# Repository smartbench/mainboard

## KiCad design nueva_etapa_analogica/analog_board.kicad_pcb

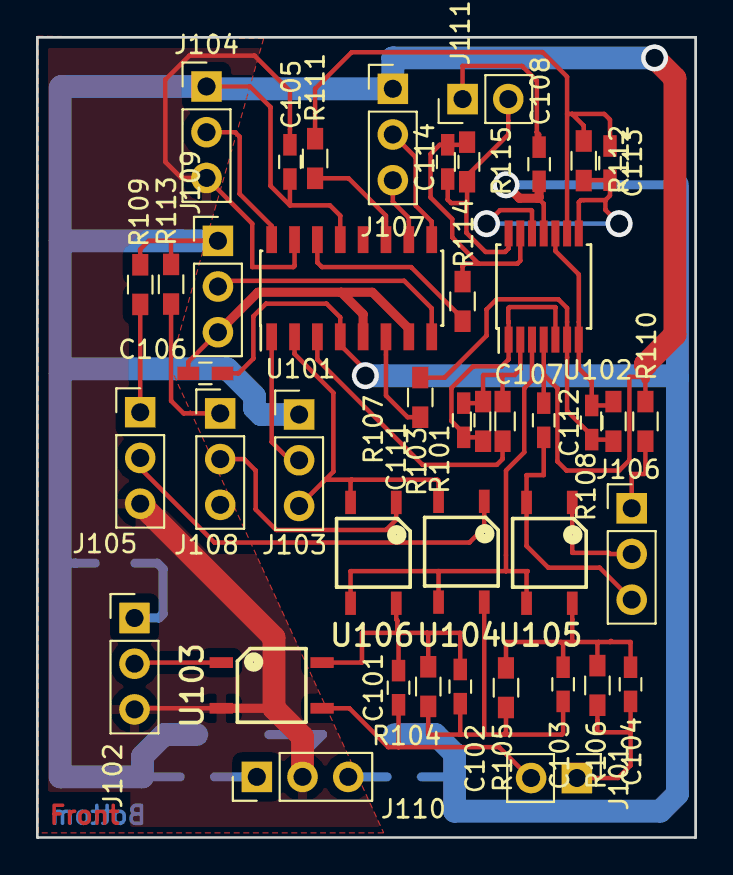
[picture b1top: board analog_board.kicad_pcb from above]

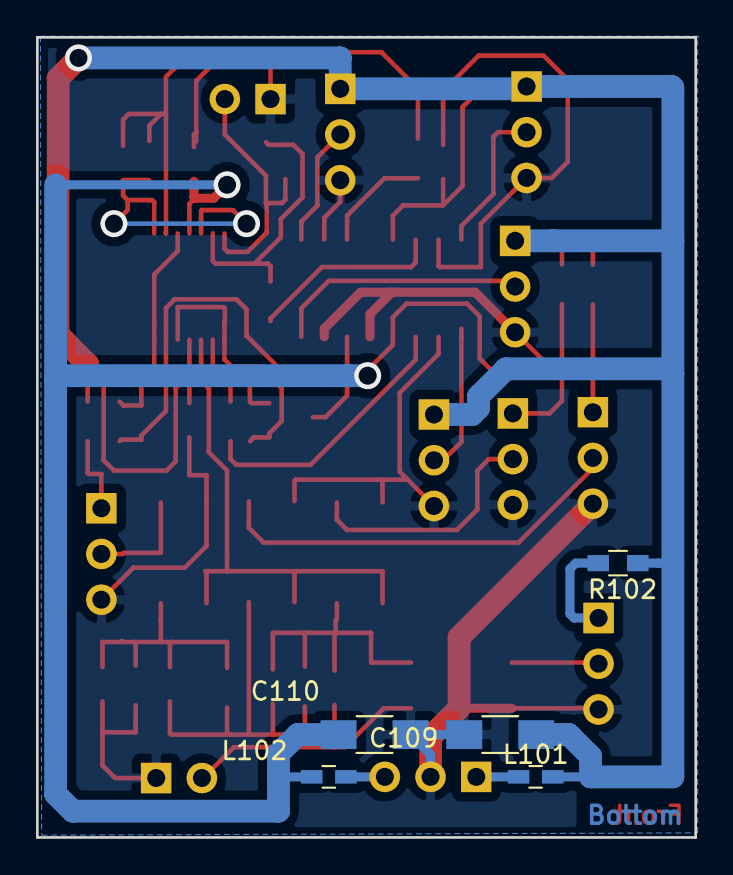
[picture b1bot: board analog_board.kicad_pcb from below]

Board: 2 copper layers, 36.6 x 44.5 mm, 48 parts (5 on the bottom side), 34 nets.

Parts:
C101, C105, C106, C107, C108: 100nF; C_0603_HandSoldering
C102: 22pF; C_0603_HandSoldering
C103: 180pF; C_0603_HandSoldering
C104: 1800pF; C_0603_HandSoldering
C109, C110: 10uF 10V Tantalum; C_1206_HandSoldering
C111, C112, C113, C114: 10pF; C_0603_HandSoldering
J101, J111: Conn_01x02; Pin_Header_Straight_1x02_Pitch2.54mm
J102, J103, J104, J105, J106, J107, J108, J109, J110: Conn_01x03; Pin_Header_Straight_1x03_Pitch2.54mm
L101, L102: BLM18AG121SN1D; C_0603_HandSoldering
R101, R107, R111, R114: 2K2; R_0603_HandSoldering
R102, R109, R110, R113: 1K; R_0603_HandSoldering
R103, R108, R112: 4K7; R_0603_HandSoldering
R104: 887K; R_0603_HandSoldering
R105: 90K9; R_0603_HandSoldering
R106, R115: 10K; R_0603_HandSoldering
U101: MAX4522CSE+; SOIC-16_3.9x9.9mm_Pitch1.27mm
U102: TLV3544; TSSOP-14_4.4x5mm_Pitch0.65mm
U103, U104, U105, U106: CPC1017N; 2.54SOP4

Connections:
/Vatt: U102.3, U104.3, U105.3, U106.3
/Vin_coupled: C101.1, C102.1, R104.2, U103.4, U106.4
GND: C104.2, C105.2, C106.1, C107.2, C108.1, C109.2, C110.1, J101.1, J102.3, J103.3, J104.3, J105.3, J106.3, J107.3, J108.3, J109.3, J110.2, J111.1, R106.1, U101.2, U101.5, U101.7, U101.10, U101.15, U103.2, U104.2, U105.2, U106.2
unnamed: C101.2, J101.2, U103.3
unnamed: C102.2, C103.1, R104.1, R105.2, U104.4
unnamed: C103.2, C104.1, R105.1, R106.2, U105.4
unnamed: C111.1, R101.2, R103.2, U102.2
unnamed: C111.2, R103.1, U102.1, U102.5
unnamed: C112.1, R107.2, R108.2, U102.6
unnamed: C112.2, R108.1, U102.7, U102.10
unnamed: C113.1, R111.2, R112.2, U102.9
unnamed: C113.2, R112.1, U102.8, U102.12
unnamed: C114.1, R114.2, R115.2, U102.13
unnamed: C114.2, J111.2, R115.1, U102.14
unnamed: J102.1, R102.1
unnamed: J102.2, U103.1
unnamed: J103.2, U101.1
unnamed: J104.2, U101.16
unnamed: J105.1, R109.1
unnamed: J105.2, U104.1
unnamed: J106.1, R110.1
unnamed: J106.2, U105.1
unnamed: J107.2, U101.9
unnamed: J108.1, R113.1
unnamed: J108.2, U106.1
unnamed: J109.2, U101.8
unnamed: J110.1, L101.1
unnamed: J110.3, L102.1
unnamed: R101.1, U101.3
unnamed: R107.1, U101.6
unnamed: R111.1, U101.11
unnamed: R114.1, U101.14
VDD: C105.1, C107.1, C109.1, J103.1, J104.1, J107.1, J109.1, L101.2, R102.2, R109.2, R110.2, R113.2, U101.13, U102.4
VSS: C106.2, C108.2, C110.2, L102.2, U101.4, U102.11

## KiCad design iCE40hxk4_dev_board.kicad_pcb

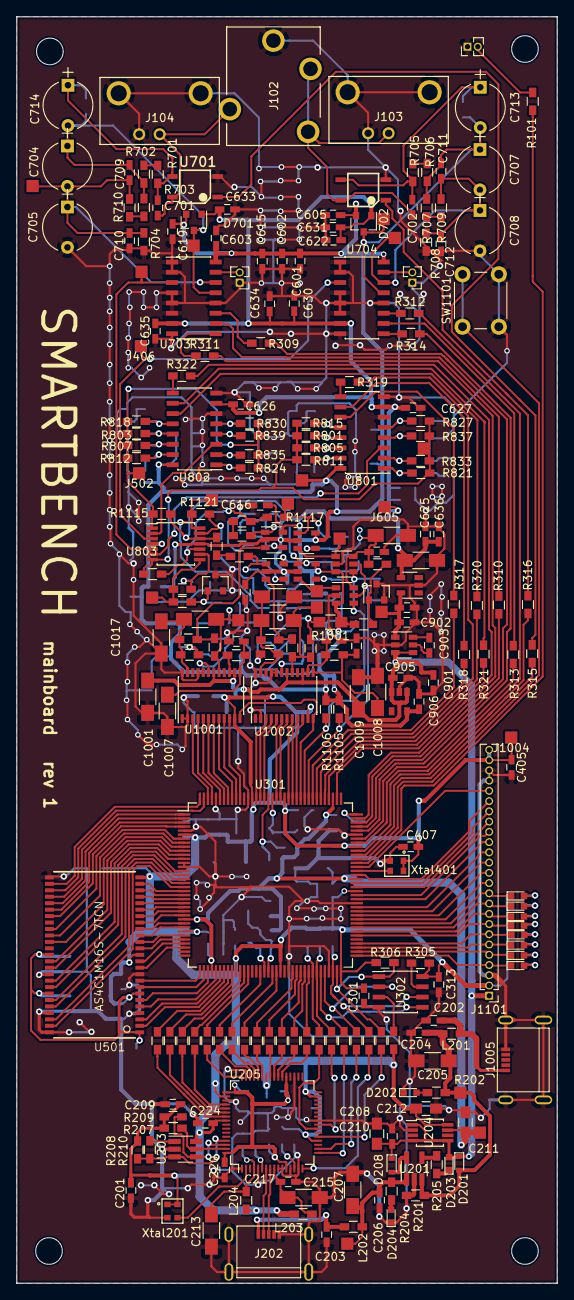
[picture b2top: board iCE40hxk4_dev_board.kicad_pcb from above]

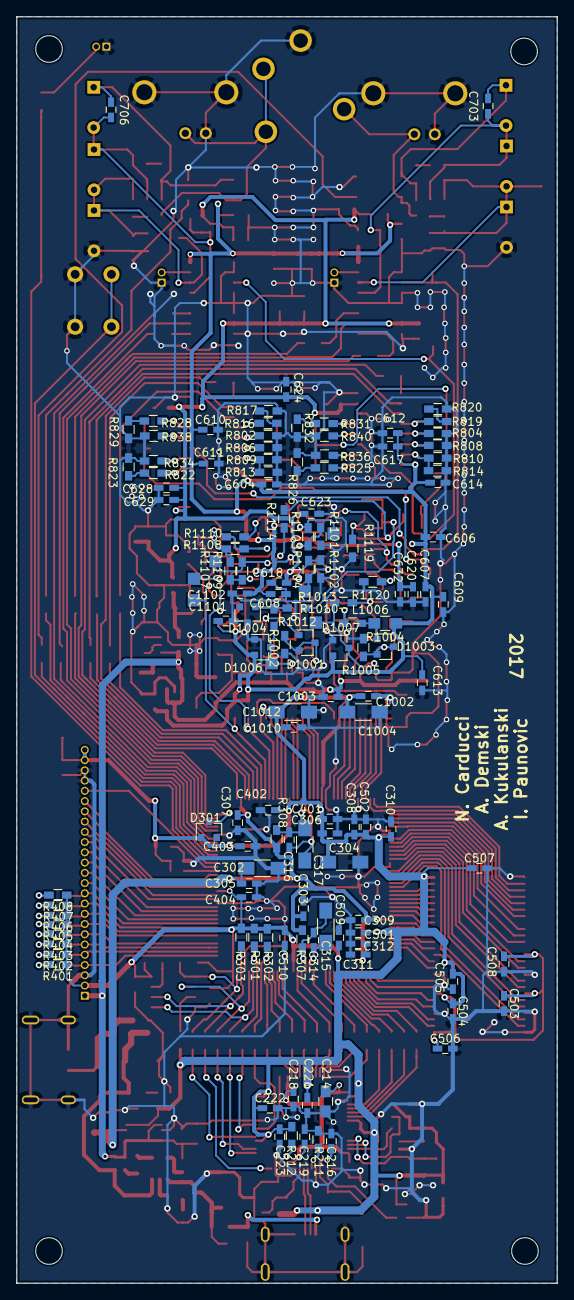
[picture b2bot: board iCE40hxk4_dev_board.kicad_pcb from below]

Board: 4 copper layers, 67.0 x 157.0 mm, 383 parts (133 on the bottom side), 266 nets.

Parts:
C201, C204, C206, C208, C209, C216, C217, C218, C219, C220, C221, C222, C223, C224, C301, C305, C307, C308, C309, C311, C313, C314, C316, C401, C402, C403, C404, C405, C407, C501, C502, C503, C504, C505, C506, C507, C508, C509, C510, C601, C603, C605, C606, C608, C612, C614, C616, C618, C619, C621, C623, C625, C627, C629, C631, C633, C635, C905, C1002, C1003, C1005, C1006, C1010, C1011, C1018, C1101, C1102: 100nF; C_0603_HandSoldering
C202, C203, C310, C312: 10nF; C_0603_HandSoldering
C205, C207, C213, C215: 4.7uF; C_1206_HandSoldering
C210, C211, C212: 2.2uF; C_0805_HandSoldering
C214: 4.7uF; C_0805_HandSoldering
C302, C304, C315, C317, C907, C1001, C1004, C1007, C1008, C1009, C1012, C1013, C1014, C1015, C1016, C1017: 10uF; C_1206_HandSoldering
C303, C306, C602, C604, C607, C609, C611, C613, C615, C617, C622, C624, C626, C628, C630, C632, C634, C636, C903, C904, C906: 1uF; C_0603_HandSoldering
C610, C620, C901, C902: 10uF; C_0603_HandSoldering
C701, C702: 100pF; C_0603_HandSoldering
C703, C706: 22pF; C_0603_HandSoldering
C704, C707: 1-3pF; CP_Radial_Tantal_D6.0mm_P5.00mm
C705, C708: 5-20pF; CP_Radial_Tantal_D6.0mm_P5.00mm
C709, C711: 180pF; C_0603_HandSoldering
C710, C712: 1800pF; C_0603_HandSoldering
C713, C714: Not used; CP_Radial_Tantal_D6.0mm_P5.00mm
D201, D208: D_Schottky_CDBURT0530LL-HF; D_0603
D202, D204, D401, D402, D403, D404, D405, D406, D407, D408: GREEN; LED_0603
D203: RED; LED_0603
D301: D_BAS21,215; D_SOT-23_ANK
D701, D702, D1006, D1007: D_Schottky_BAT54S-7-F; SOT-23
D1001, D1003: LM4040DYM3-2.5-TR; SOT-23
D1002: LM4041EIM3-1.2/NOPB; SOT-23
D1004, D1005: D_Schottky_BAT54-7-F; D_SOT-23_ANK
J101, J601, J602: CONN_01X02; Pin_Header_Straight_1x02_Pitch1.27mm
J102: Jack Estereo; KobiConn_161-3509-E_Jack_3.5mm
J103, J104: CONN_COAXIAL; BNC_1-1337543-0
J105, J106, J107, J108: MountingHole
J202: USB_OTG; USB_Micro-B_47642-0001
J401, J402, J403, J404, J405, J406, J501, J502, J603, J604, J605, J701, J702, J705, J706, J801, J802, J803, J804, J805, J806, J807, J808, J809, J810, J1001, J1002, J1003, J1004: Testpoint; TestPoint
J1005: USB_EXT; USB_Micro-B_47642-0001
J1101: CONN_01X25; Pin_Header_Straight_1x25_Pitch1.27mm
L201, L202, L203, L204: L_BLM18BA750SZ1D; L_0603_HandSoldering
L1001, L1002, L1003, L1004, L1005, L1006, L1007: L_BLM18AG121SN1D; L_0603_HandSoldering
R101, R201, R207, R209, R210, R301, R302, R303, R304, R305, R306, R704, R708, R1105, R1106, R1107, R1108, R1109, R1110: 10K; R_0603_HandSoldering
R202, R204, R205: 1K5; R_0603_HandSoldering
R208, R829, R832: 2K2; R_0603_HandSoldering
R211: 12K; R_0603_HandSoldering
R212, R309, R310, R311, R312, R313, R314, R315, R316, R317, R318, R319, R320, R321, R322, R827, R830, R1115, R1118: 1K; R_0603_HandSoldering
R213, R214, R215, R216, R217, R218, R219, R220, R221, R222, R223, R224, R225, R226, R227, R228, R229, R230, R231, R709, R710, R801, R803, R1002, R1005, R1103, R1104: 0R; R_0603_HandSoldering
R307, R308, R821, R823, R824, R826: 100R; R_0603_HandSoldering
R401, R402, R403, R404, R405, R406, R407, R408: 680R; R_0603_HandSoldering
R701, R705: 13K; R_0603_HandSoldering
R702, R706: 887K; R_0603_HandSoldering
R703, R707: 90K9; R_0603_HandSoldering
R802, R804, R1101, R1102: Let it open; R_0603_HandSoldering
R805, R806, R807, R808, R1010, R1011: 470R; R_0603_HandSoldering
R809, R810, R813, R814, R816, R819, R822, R825: 1K8; R_0603_HandSoldering
R811, R812, R815, R817, R818, R820, R1003, R1012, R1013: 220R; R_0603_HandSoldering
R828, R831: 47K; R_0603_HandSoldering
R833, R834, R835, R836, R837, R838, R839, R840: Not used; R_0603_HandSoldering
R1001, R1004: 50R; R_0805_HandSoldering
R1006, R1007, R1008, R1009, R1113, R1116: 4K7; R_0603_HandSoldering
R1111, R1112: 330R; R_0603_HandSoldering
R1114, R1117: 1K2; R_0603_HandSoldering
R1119, R1120: 6K8; R_0603_HandSoldering
R1121, R1122: 62K; R_0603_HandSoldering
SW1101: SW_Push; SW_PUSH_6mm_h4.3mm
U201: MIC2005A-2YM5; SOT-23-5_HandSoldering
U203: 93LC56BT-I/OT; SOT-23-6_Handsoldering
U204: MIC5355-S4YMME; MSOP-8_3x3mm_Pitch0.65mm
U205: FT2232H; LQFP-64_10x10mm_Pitch0.5mm
U301: iCE40-HX4K-TQ144; LQFP-144_20x20mm_Pitch0.5mm
U302: FLASH 2Mb; SOIC-8_3.9x4.9mm_Pitch1.27mm
U501: AS4C1M16S-7TCN; TSOP50-II
U701, U702: CPC1017N; 2.54SOP4
U703, U704, U801, U802: CD4051BM96; SOIC-16_3.9x9.9mm_Pitch1.27mm
U803: TLV3544IPWR; TSSOP-14_4.4x5mm_Pitch0.65mm
U901: LM2776DBVR; SOT-23-6
U902: MIC5317-2.5YM5-TR; SC-74(5-pins)
U903: TPS72325DBVR; SOT-23-5
U1001, U1002: ADC1175; TSSOP-24_4.4x7.8mm_Pitch0.65mm
U1101, U1102, U1105, U1106: MIC7300; SOT-23-5
U1103, U1104: MCP4716; SOT-23-6
Xtal201, Xtal401: LFSPXO019966; VLGA_4_2.5x2.0mm

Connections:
+1.8V: C214.1, C218.1, C219.1, C220.1, U205.12, U205.37, U205.49, U205.64
+3V3: C201.1, C209.1, C212.1, C221.1, C222.1, C223.1, C224.1, C301.1, C304.1, C306.1, C308.1, C310.1, C313.1, C401.1, C402.1, C403.1, C404.1, C405.1, C407.1, C501.1, C502.1, C503.1, C504.1, C505.1, C506.1, C507.1, C508.1, C509.1, C510.1, C1002.2, C1004.1, C1010.2, C1012.1, D301.2, J1004.1, J1101.2, J1101.24, J1101.25, L203.1, L204.1, R207.1, R209.1, R210.1, R212.2, R301.1, R302.1, R303.1, R304.1, R305.1, R306.1, R401.1, R402.1, R403.1, R404.1, R405.1, R406.1, R407.1, R408.1, U203.6, U204.8, U205.20, U205.31, U205.42, U205.50, U205.56, U301.6, U301.30, U301.46, U301.57, U301.72, U301.89, U301.100, U301.123, U301.131, U302.8, U501.1, U501.7, U501.13, U501.25, U501.38, U501.44, U1001.11, U1002.11, Xtal201.1, Xtal201.4, Xtal401.1, Xtal401.4
+5V: C208.1, C210.1, C901.1, C905.1, C1001.1, C1003.2, C1009.1, C1011.2, D201.1, D203.2, D208.1, J1101.1, L1001.1, L1002.1, U204.1, U204.4, U204.5, U901.3, U901.4, U902.1, U902.3, U1001.14, U1001.15, U1001.18, U1002.14, U1002.15, U1002.18
/Analog front end/-5V: C902.1, C904.2, J603.1, U901.1, U903.5
/Analog front end/ADC/5V0_D1: C1005.2, C1007.1, L1001.2, U1001.13
/Analog front end/ADC/5V0_D2: C1006.2, C1008.1, L1002.2, U1002.13
/Analog front end/ADC/CHA_V_REF_BOTTOM: C1016.2, C1017.1, L1007.2, R1009.1, U1001.23
/Analog front end/ADC/CHA_V_REF_TOP: C1016.1, J702.1, L1006.2, R1008.2, U1001.17
/Analog front end/ADC/CHB_V_REF_BOTTOM: C1013.2, C1014.1, L1004.2, R1007.1, U1002.23
/Analog front end/ADC/CHB_V_REF_TOP: C1013.1, J701.1, L1003.2, R1006.2, U1002.17
/Analog front end/ADC_CLK: U301.119, U1001.12, U1002.12
/Analog front end/ATTENUATION/CHA_ATT_20dB: C703.2, C704.1, C709.1, C714.2, D701.3, J403.1, R702.2, R703.1, U703.13
/Analog front end/ATTENUATION/CHA_ATT_40dB: C704.2, C705.1, C709.2, C710.1, J404.1, R704.1, R710.1, U703.14
/Analog front end/ATTENUATION/CHA_ATT_SEL_0: R309.1, U703.11
/Analog front end/ATTENUATION/CHA_ATT_SEL_1: R310.1, U703.10
/Analog front end/ATTENUATION/CHA_ATT_SEL_2: R311.1, U703.9
/Analog front end/ATTENUATION/CHA_DC_COUPLING: R315.1, U701.1
/Analog front end/ATTENUATION/CHB_ATT_20dB: C706.2, C707.1, C711.1, C713.2, D702.3, J402.1, R706.2, R707.1, U704.13
/Analog front end/ATTENUATION/CHB_ATT_40dB: C707.2, C708.1, C711.2, C712.1, J401.1, R708.1, R709.1, U704.14
/Analog front end/ATTENUATION/CHB_ATT_SEL_0: R312.1, U704.11
/Analog front end/ATTENUATION/CHB_ATT_SEL_1: R313.1, U704.10
/Analog front end/ATTENUATION/CHB_ATT_SEL_2: R314.1, U704.9
/Analog front end/ATTENUATION/CHB_DC_COUPLING: R316.1, U702.1
/Analog front end/CHA_ATT_OUT: J405.1, U703.3, U803.5
/Analog front end/CHA_ATT_SEL_0: R309.2, U301.105
/Analog front end/CHA_ATT_SEL_1: R310.2, U301.106
/Analog front end/CHA_ATT_SEL_2: R311.2, U301.107
/Analog front end/CHA_DAC: J804.1, U1104.1, U1106.3
/Analog front end/CHA_DC_COUPLING: R315.2, U301.98
/Analog front end/CHA_GAIN_SEL_0: R317.2, U301.116
/Analog front end/CHA_GAIN_SEL_1: R318.2, U301.115
/Analog front end/CHA_GAIN_SEL_2: R319.2, U301.114
/Analog front end/CHA_OFFSET: J806.1, R1110.1, R1117.2, U1106.1
/Analog front end/CHA_OFFSET_OUT: J808.1, R1011.2, R1122.1, U803.8
/Analog front end/CHA_PGA_OUT: J501.1, R801.2, R805.1, R811.1, R815.1, R821.1, R827.1, R833.1, R837.1, R1118.2, U803.7
/Analog front end/CHA_VREF_CENT: R1008.1, R1009.2, U1101.3
/Analog front end/CHB_ATT_OUT: J406.1, U704.3, U803.3
/Analog front end/CHB_ATT_SEL_0: R312.2, U301.101
/Analog front end/CHB_ATT_SEL_1: R313.2, U301.102
/Analog front end/CHB_ATT_SEL_2: R314.2, U301.104
/Analog front end/CHB_DAC: J803.1, U1103.1, U1105.3
/Analog front end/CHB_DC_COUPLING: R316.2, U301.99
/Analog front end/CHB_GAIN_SEL_0: R320.2, U301.113
/Analog front end/CHB_GAIN_SEL_1: R321.2, U301.112
/Analog front end/CHB_GAIN_SEL_2: R322.2, U301.110
/Analog front end/CHB_OFFSET: J805.1, R1109.1, R1114.2, U1105.1
/Analog front end/CHB_OFFSET_OUT: J807.1, R1010.2, R1121.1, U803.14
/Analog front end/CHB_PGA_OUT: J502.1, R803.2, R807.1, R812.1, R818.1, R824.1, R830.1, R835.1, R839.1, R1115.2, U803.1
/Analog front end/CHB_VREF_CENT: R1006.1, R1007.2, U1102.3
/Analog front end/OFFSET/CHA_V_OFFSET_FIJO: J802.1, R1103.1, R1112.2, U1101.1
/Analog front end/OFFSET/CHB_V_OFFSET_FIJO: J801.1, R1104.1, R1111.2, U1102.1
/Analog front end/PGA/CHA_G0: R801.1, R802.2, U801.13
/Analog front end/PGA/CHA_G1: R805.2, R806.1, U801.14
/Analog front end/PGA/CHA_G2: R809.1, R811.2, R813.1, U801.15
/Analog front end/PGA/CHA_G3: R815.2, R816.2, U801.12
/Analog front end/PGA/CHA_G4: R821.2, R822.1, U801.1
/Analog front end/PGA/CHA_G5: R827.2, R828.1, U801.5
/Analog front end/PGA/CHA_G6: R833.2, R834.1, U801.2
/Analog front end/PGA/CHA_G7: R837.2, R838.1, U801.4
/Analog front end/PGA/CHA_GAIN_SEL_0: R317.1, U801.11
/Analog front end/PGA/CHA_GAIN_SEL_1: R318.1, U801.10
/Analog front end/PGA/CHA_GAIN_SEL_2: R319.1, U801.9
/Analog front end/PGA/CHB_G0: R803.1, R804.2, U802.13
/Analog front end/PGA/CHB_G1: R807.2, R808.1, U802.14
/Analog front end/PGA/CHB_G2: R810.1, R812.2, R814.1, U802.15
/Analog front end/PGA/CHB_G3: R818.2, R819.2, U802.12
/Analog front end/PGA/CHB_G4: R824.2, R825.2, U802.1
/Analog front end/PGA/CHB_G5: R830.2, R831.1, U802.5
/Analog front end/PGA/CHB_G6: R835.2, R836.1, U802.2
/Analog front end/PGA/CHB_G7: R839.2, R840.1, U802.4
/Analog front end/PGA/CHB_GAIN_SEL_0: R320.1, U802.11
/Analog front end/PGA/CHB_GAIN_SEL_1: R321.1, U802.10
/Analog front end/PGA/CHB_GAIN_SEL_2: R322.1, U802.9
/Analog front end/VDD_A: C601.2, C602.2, C603.2, C604.2, C605.2, C606.2, C607.2, C608.2, C609.2, C610.1, C611.2, C612.2, C613.2, C614.2, C615.2, C616.2, C617.2, C619.2, C906.1, C1101.2, C1102.2, D701.2, D702.2, D1006.2, D1007.2, J604.1, R1001.1, R1003.2, R1004.1, R1105.1, R1106.1, U703.16, U704.16, U801.16, U802.16, U803.4, U902.5, U1101.5, U1102.5, U1103.3, U1104.3, U1105.5, U1106.5
/Analog front end/VSS_A: C618.2, C620.1, C621.2, C622.2, C623.2, C624.2, C625.2, C626.2, C627.2, C628.2, C629.2, C630.2, C631.2, C632.2, C633.2, C634.2, C635.2, C636.2, C907.2, D701.1, D702.1, J605.1, U703.7, U704.7, U801.7, U802.7, U803.11, U903.4, U1101.2, U1102.2, U1105.2, U1106.2
/Analog front end/V_REF_DAC: C1015.1, C1018.2, L1005.2, R1107.2, R1108.2, U1103.6, U1104.6
/CHA: C701.2, J102.2, J104.1, U701.4
/CHB: C702.2, J102.3, J102.4, J103.1, U702.4
/FPGA_PROGRAMMING+POWER/+1.2V: C211.1, C302.1, C303.1, C305.1, C307.1, C309.1, C311.1, C312.1, J1003.1, R307.1, R308.1, U204.7, U301.27, U301.40, U301.92, U301.111
/FPGA_PROGRAMMING+POWER/CDONE: R217.1, R302.2, U301.65
/FPGA_PROGRAMMING+POWER/CRESET: R218.1, R301.2, U301.66
/FPGA_PROGRAMMING+POWER/MISO: R215.1, U301.68, U302.2
/FPGA_PROGRAMMING+POWER/MOSI: R214.1, U301.67, U302.5
/FPGA_PROGRAMMING+POWER/SCK: R213.1, R303.2, U301.70, U302.6
/FPGA_PROGRAMMING+POWER/SS: R216.1, R306.2, U301.71, U302.1
/RAM+LEFT_BOTTOM_BANKs/A0: U301.23, U501.21
/RAM+LEFT_BOTTOM_BANKs/A1: U301.22, U501.22
/RAM+LEFT_BOTTOM_BANKs/A2: U301.21, U501.23
/RAM+LEFT_BOTTOM_BANKs/A3: U301.20, U501.24
/RAM+LEFT_BOTTOM_BANKs/A4: U301.144, U501.27
/RAM+LEFT_BOTTOM_BANKs/A5: U301.143, U501.28
/RAM+LEFT_BOTTOM_BANKs/A6: U301.1, U501.29
/RAM+LEFT_BOTTOM_BANKs/A7: U301.2, U501.30
/RAM+LEFT_BOTTOM_BANKs/A8: U301.3, U501.31
/RAM+LEFT_BOTTOM_BANKs/A9: U301.4, U501.32
/RAM+LEFT_BOTTOM_BANKs/A10: U301.24, U501.20
/RAM+LEFT_BOTTOM_BANKs/A11: U301.25, U501.19
/RAM+LEFT_BOTTOM_BANKs/CKE: U301.7, U501.34
/RAM+LEFT_BOTTOM_BANKs/CLK: U301.8, U501.35
/RAM+LEFT_BOTTOM_BANKs/D0: R219.1, U301.64
/RAM+LEFT_BOTTOM_BANKs/D1: R220.1, U301.63
/RAM+LEFT_BOTTOM_BANKs/D2: R221.1, U301.62
/RAM+LEFT_BOTTOM_BANKs/D3: R222.1, U301.61
/RAM+LEFT_BOTTOM_BANKs/D4: R223.1, U301.60
/RAM+LEFT_BOTTOM_BANKs/D5: R224.1, U301.56
/RAM+LEFT_BOTTOM_BANKs/D6: R225.1, U301.55
/RAM+LEFT_BOTTOM_BANKs/D7: R226.1, U301.52
/RAM+LEFT_BOTTOM_BANKs/DQ0: U301.43, U501.2
/RAM+LEFT_BOTTOM_BANKs/DQ1: U301.42, U501.3
/RAM+LEFT_BOTTOM_BANKs/DQ2: U301.41, U501.5
/RAM+LEFT_BOTTOM_BANKs/DQ3: U301.39, U501.6
/RAM+LEFT_BOTTOM_BANKs/DQ4: U301.38, U501.8
/RAM+LEFT_BOTTOM_BANKs/DQ5: U301.37, U501.9
/RAM+LEFT_BOTTOM_BANKs/DQ6: U301.34, U501.11
/RAM+LEFT_BOTTOM_BANKs/DQ7: U301.33, U501.12
/RAM+LEFT_BOTTOM_BANKs/DQ8: U301.10, U501.39
/RAM+LEFT_BOTTOM_BANKs/DQ9: U301.11, U501.40
/RAM+LEFT_BOTTOM_BANKs/DQ10: U301.12, U501.42
/RAM+LEFT_BOTTOM_BANKs/DQ11: U301.15, U501.43
/RAM+LEFT_BOTTOM_BANKs/DQ12: U301.16, U501.45
/RAM+LEFT_BOTTOM_BANKs/DQ13: U301.17, U501.46
/RAM+LEFT_BOTTOM_BANKs/DQ14: U301.18, U501.48
/RAM+LEFT_BOTTOM_BANKs/DQ15: U301.19, U501.49
/RAM+LEFT_BOTTOM_BANKs/LDQM: U301.32, U501.14
/RAM+LEFT_BOTTOM_BANKs/SIWU: R231.1, U301.44
/RAM+LEFT_BOTTOM_BANKs/UDQM: U301.9, U501.36
/RAM+LEFT_BOTTOM_BANKs/~CAS: U301.29, U501.16
/RAM+LEFT_BOTTOM_BANKs/~CS: U301.26, U501.18
/RAM+LEFT_BOTTOM_BANKs/~RAS: U301.28, U501.17
/RAM+LEFT_BOTTOM_BANKs/~RD: R229.1, U301.47
/RAM+LEFT_BOTTOM_BANKs/~RXF: R227.1, U301.49
/RAM+LEFT_BOTTOM_BANKs/~TXE: R228.1, U301.48
/RAM+LEFT_BOTTOM_BANKs/~WE: U301.31, U501.15
/RAM+LEFT_BOTTOM_BANKs/~WR: R230.1, U301.45
/RIGHT_TOP_BANKs/ADC_0: U301.120, U1002.10
/RIGHT_TOP_BANKs/ADC_1: U301.121, U1002.9
/RIGHT_TOP_BANKs/ADC_2: U301.122, U1002.8
/RIGHT_TOP_BANKs/ADC_3: U301.124, U1002.7
/RIGHT_TOP_BANKs/ADC_4: U301.125, U1002.6
/RIGHT_TOP_BANKs/ADC_5: U301.128, U1002.5
/RIGHT_TOP_BANKs/ADC_6: U301.129, U1002.4
/RIGHT_TOP_BANKs/ADC_7: U301.130, U1002.3
/RIGHT_TOP_BANKs/ADC_8: U301.134, U1001.10
/RIGHT_TOP_BANKs/ADC_9: U301.135, U1001.9
/RIGHT_TOP_BANKs/ADC_10: U301.136, U1001.8
/RIGHT_TOP_BANKs/ADC_11: U301.137, U1001.7
/RIGHT_TOP_BANKs/ADC_12: U301.138, U1001.6
/RIGHT_TOP_BANKs/ADC_13: U301.139, U1001.5
/RIGHT_TOP_BANKs/ADC_14: U301.141, U1001.4
/RIGHT_TOP_BANKs/ADC_15: U301.142, U1001.3
/RIGHT_TOP_BANKs/IOR_109: D401.1, J1101.4, U301.73
/RIGHT_TOP_BANKs/IOR_110: D402.1, J1101.5, U301.74
/RIGHT_TOP_BANKs/IOR_111: D403.1, J1101.6, U301.75
/RIGHT_TOP_BANKs/IOR_112: D404.1, J1101.7, U301.76
/RIGHT_TOP_BANKs/IOR_114: D405.1, J1101.8, U301.78
/RIGHT_TOP_BANKs/IOR_115: D406.1, J1101.9, U301.79
/RIGHT_TOP_BANKs/IOR_116: D407.1, J1101.10, U301.80
/RIGHT_TOP_BANKs/IOR_117: D408.1, J1101.11, U301.81
/RIGHT_TOP_BANKs/IOR_118: J1101.12, U301.82
/RIGHT_TOP_BANKs/IOR_119: J1101.13, U301.83
/RIGHT_TOP_BANKs/IOR_120: J1101.14, U301.84
/RIGHT_TOP_BANKs/IOR_128: J1101.15, U301.85
/RIGHT_TOP_BANKs/IOR_136: J1101.16, U301.87
/RIGHT_TOP_BANKs/IOR_137: J1101.17, U301.88
/RIGHT_TOP_BANKs/IOR_138: J1101.18, U301.90
/RIGHT_TOP_BANKs/IOR_139: J1101.19, U301.91
/RIGHT_TOP_BANKs/IOR_140: J1101.20, U301.93
/RIGHT_TOP_BANKs/IOR_144: J1101.21, U301.95
/RIGHT_TOP_BANKs/IOT_146: R101.1, U301.96
/RIGHT_TOP_BANKs/IOT_174: J809.1, R1105.2, U301.117, U1103.5, U1104.5
/RIGHT_TOP_BANKs/IOT_177: J810.1, R1106.2, U301.118, U1103.4, U1104.4
/RIGHT_TOP_BANKs/OSC: U301.94, Xtal401.3
/USB+OSCILLATOR+REGULATOR/D+: J202.3, U205.8
/USB+OSCILLATOR+REGULATOR/D-: J202.2, U205.7
/USB+OSCILLATOR+REGULATOR/EECLK: R209.2, U203.4, U205.62
/USB+OSCILLATOR+REGULATOR/EECS: R207.2, U203.5, U205.63
/USB+OSCILLATOR+REGULATOR/EEDATA: R208.1, R210.2, U203.3, U205.61
/USB+OSCILLATOR+REGULATOR/Vbus_filtered: C206.1, C207.1, J1002.1, L202.2, R204.2, U201.1
/USB+OSCILLATOR+REGULATOR/Vext_filtered: C204.1, C205.1, D201.2, J1001.1, L201.2, R201.1, R202.1, U201.3
GND: C201.2, C202.2, C203.2, C204.2, C205.2, C206.2, C207.2, C208.2, C209.2, C210.2, C211.2, C212.2, C213.2, C214.2, C215.2, C216.2, C217.2, C218.2, C219.2, C220.2, C221.2, C222.2, C223.2, C224.2, C301.2, C302.2, C303.2, C304.2, C305.2, C306.2, C307.2, C308.2, C309.2, C310.2, C311.2, C312.2, C313.2, C401.2, C402.2, C403.2, C404.2, C405.2, C407.2, C501.2, C502.2, C503.2, C504.2, C505.2, C506.2, C507.2, C508.2, C509.2, C510.2, C601.1, C602.1, C603.1, C604.1, C605.1, C606.1, C607.1, C608.1, C609.1, C610.2, C611.1, C612.1, C613.1, C614.1, C615.1, C616.1, C617.1, C618.1, C619.1, C620.2, C621.1, C622.1, C623.1, C624.1, C625.1, C626.1, C627.1, C628.1, C629.1, C630.1, C631.1, C632.1, C633.1, C634.1, C635.1, C636.1, C705.2, C708.2, C710.2, C712.2, C901.2, C902.2, C904.1, C905.2, C906.2, C907.1, C1001.2, C1002.1, C1003.1, C1004.2, C1005.1, C1006.1, C1007.2, C1008.2, C1009.2, C1010.1, C1011.1, C1012.2, C1014.2, C1015.2, C1017.2, C1018.1, C1101.1, C1102.1, D202.1, D204.1, D1002.2, D1002.3, D1004.1, D1005.1, D1006.1, D1007.1, J101.1, J102.1, J103.2, J104.2, J202.5, J202.6, J601.1, J602.1, J1005.5, J1005.6, J1101.3, J1101.22, J1101.23, R201.2, R211.2, R704.2, R708.2, R802.1, R804.1, R806.2, R808.2, R809.2, R810.2, R813.2, R814.2, R817.2, R820.2, R823.2, R826.2, R829.2, R832.2, R834.2, R836.2, R838.2, R840.2, R1002.1, R1005.1, R1101.2, R1102.2, R1119.2, R1120.2, SW1101.2, U201.2, U203.2, U204.2, U205.1, U205.5, U205.10, U205.11, U205.13, U205.15, U205.25, U205.35, U205.47, U205.51, U301.5, U301.13, U301.14, U301.59, U301.69, U301.86, U301.103, U301.132, U301.140, U302.4, U501.4, U501.10, U501.26, U501.41, U501.47, U501.50, U701.2, U702.2, U703.1, U703.2, U703.4, U703.5, U703.6, U703.8, U703.12, U704.1, U704.2, U704.4, U704.5, U704.6, U704.8, U704.12, U801.6, U801.8, U802.6, U802.8, U901.2, U902.2, U903.2, U1001.1, U1001.2, U1001.20, U1001.21, U1001.24, U1002.1, U1002.2, U1002.20, U1002.21, U1002.24, U1103.2, U1104.2, Xtal201.2, Xtal401.2
unnamed: C202.1, J1005.1, L201.1
unnamed: C203.1, J202.1, L202.1
unnamed: C213.1, C216.1, L204.2, U205.4
unnamed: C215.1, C217.1, L203.2, U205.9
unnamed: C314.1, C315.1, R307.2, U301.54
unnamed: C314.2, C315.2, U301.53
unnamed: C316.1, C317.1, R308.2, U301.126
unnamed: C316.2, C317.2, U301.127
unnamed: C701.1, C703.1, C714.1, R701.1, U701.3
unnamed: C702.1, C706.1, C713.1, R705.1, U702.3
unnamed: C903.1, U901.5
unnamed: C903.2, U901.6
unnamed: D202.2, R202.2
unnamed: D203.1, R205.1
unnamed: D204.2, R204.1
unnamed: D208.2, U201.5
unnamed: D301.1, U301.108
unnamed: D401.2, R401.2
unnamed: D402.2, R402.2
unnamed: D403.2, R403.2
unnamed: D404.2, R404.2
unnamed: D405.2, R405.2
unnamed: D406.2, R406.2
unnamed: D407.2, R407.2
unnamed: D408.2, R408.2
unnamed: D1001.1, L1003.1, R1001.2
unnamed: D1001.2, D1001.3, L1004.1, R1002.2
unnamed: D1002.1, L1005.1, R1003.1
unnamed: D1003.1, L1006.1, R1004.2
unnamed: D1003.2, D1003.3, L1007.1, R1005.2
unnamed: D1004.2, R1010.1, R1012.2
unnamed: D1005.2, R1011.1, R1013.2
unnamed: D1006.3, J705.1, R1012.1, U1002.19
unnamed: D1007.3, J706.1, R1013.1, U1001.19
unnamed: J101.2, R101.2
unnamed: J601.2, U703.15
unnamed: J602.2, U704.15
unnamed: R205.2, U201.4
unnamed: R208.2, U203.1
unnamed: R211.1, U205.6
unnamed: R212.1, U205.14
unnamed: R213.2, U205.16
unnamed: R214.2, U205.17
unnamed: R215.2, U205.18
unnamed: R216.2, U205.21
unnamed: R217.2, U205.23
unnamed: R218.2, U205.24
unnamed: R219.2, U205.38
unnamed: R220.2, U205.39
unnamed: R221.2, U205.40
unnamed: R222.2, U205.41
unnamed: R223.2, U205.43
unnamed: R224.2, U205.44
unnamed: R225.2, U205.45
unnamed: R226.2, U205.46
unnamed: R227.2, U205.48
unnamed: R228.2, U205.52
unnamed: R229.2, U205.53
unnamed: R230.2, U205.54
unnamed: R231.2, U205.55
unnamed: R304.2, U302.3
unnamed: R305.2, U302.7
unnamed: R701.2, R702.1
unnamed: R703.2, R710.2
unnamed: R705.2, R706.1
unnamed: R707.2, R709.2
unnamed: R816.1, R817.1
unnamed: R819.1, R820.1
unnamed: R822.2, R823.1
unnamed: R825.1, R826.1
unnamed: R828.2, R829.1
unnamed: R831.2, R832.1
unnamed: R1101.1, R1103.2, U1101.4
unnamed: R1102.1, R1104.2, U1102.4
unnamed: R1107.1, R1109.2, U1105.4
unnamed: R1108.1, R1110.2, U1106.4
unnamed: R1111.1, R1113.2
unnamed: R1112.1, R1116.2
unnamed: R1113.1, R1114.1, R1115.1, U803.12
unnamed: R1116.1, R1117.1, R1118.1, U803.10
unnamed: R1119.1, R1121.2, U803.13
unnamed: R1120.1, R1122.2, U803.9
unnamed: SW1101.1, U301.97
unnamed: U205.2, Xtal201.3
unnamed: U801.3, U803.6
unnamed: U802.3, U803.2

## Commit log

2017-03-30 Commit inicial. Agregado esquematico tentativo
2017-03-31 Agregada alimentacion externa y seleccion entre bus/self powered. Agregado buffer distribucion clock
2017-03-31 Agregando DRAM...
2017-03-31 Minor fixes and the gitignore was removed
2017-04-04 Reordered IO connections to FPGA
2017-04-06 Added part numbers of sheet USB+...
2017-04-07 Added part number and specifications on all sheets
2017-04-09 Reordered connections again. Option 1: RAM at left bank, some connections at left and top banks.
2017-04-13 Minnor fixes
2017-04-17 The schematic is now free of any ERC error. Not connected and power flags added. No more global power pins, hierarchical labels used for power connections. TODO list: -Check if all footpritns are alr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
2017-04-18 First netlist export
2017-04-20 Added three indicator LEDs. Two green leds, one indicating if usb power is connected, and the other one indicating if the external power source is connected. One red led indicating if fault condition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
2017-04-21 Fist approach of board placement
2017-04-21 Clk's buffers were removed and pcb routing was started
2017-04-22 Front-end first commit
2017-04-23 Agregados MPN,datasheet a librerías existentes. Creadas librerías con array de diodos schottky, muxes 8:1 y solid state relay. Pines de alimentación de mux puestos visibles. Cambiada posición de C va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
2017-04-24 Separando en bloques, completando etapa de atenuación, de ganacia variable, de offset y entrada al adc.
2017-04-25 Agregada una protección para la entrada del ADC. Etapa de offset modificada. REVISAR (just in case ...).
2017-05-07 Placing de algunos capas de acople y otras giladas
2017-05-09 Agregados reguladores fuente alimentación. Agregados varios labels. * El regulador negativo es de -3V (en vez de -3.3V). Why? Money. to do next: referencias de tensión.
2017-05-10 Agregados reguladores de tensión 2.5V (LM4040) y 1.225V (LM4041). todo: filtro Vref todo: Circuito DAC
2017-05-12 Cambios menores
2017-05-13 Changed MC2005 led fault, because it's an active low output and it's not active high. Placing of some capacitors and resistors. Check if it's possible to power the fpga in two layers (both 3.3 and 1.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
2017-05-14 cambio referencia adc (doble)
2017-05-14 Cambiado en inversor por uno de 200mA, así como sus respectivos capacitores. Falta: DAC Falta: elegir modelo capacitores
2017-05-25 Continued with routing....
2017-05-26 Continued with routing...
2017-05-27 Replacement of many components. It's not finished
2017-05-29 Agregado el DAC (MCP4716). Corregida la masa del mux. Asignados algunos footprints.
2017-05-29 agregados capas de desacople de ICs
2017-05-29 Se conecta la tensión 5V a los conectores (right y left) y se cambia de nombre de un componente MIC2005A-2 -> MIC2005A-2YM5
2017-05-30 Part Number de Capacitores de bypass
2017-05-30 Cambiados valores de resistores y capacitores Vref_ADC
2017-06-02 pequeños cambios
2017-06-02 Solved problem with power distribution.
2017-06-05 Cambiados labels globales por jerárquicos. Agregadas ganancias de yapa en etapa PGA.
2017-06-05 Agregados valores de resistencias PGA.
2017-06-05 corregido error en el mic5270.
2017-06-13 Routing
2017-06-15 Se chequean y asignan footprints de la power supply
2017-06-15 Faltó agregar los archivos en el commit anterior
2017-06-24 Ruteo de la parte digital completo. Falta revision y ordenar el silk
2017-07-11 Completed part selection of analog board. Merged analog and digital boards.
2017-07-11 Footprint config added to analog merge
2017-07-11 No more DRC errors :)
2017-07-12 Started final routing ...
2017-07-15 Ended placing (?)
2017-07-15 Continued with routing. It is all connected now, but need a revision, DRC check, etc ...
2017-08-01 Assignement of FPGA pins for analog stage control
2017-08-04 Startin routing the analog side of the force
2017-08-05 Minor changes
2017-08-05 Added reset button. Minimal changes in routing.
2017-08-08 minimal advance in routing
2017-08-09 advanced more in routing
2017-08-11 Changed DAC part number
2017-08-15 Almost finish
2017-08-15 Changed part number of DAC (different dir). Connected ADC_OE to GND.
2017-08-15 Added reset button. Delated unused fpga analog control connections. Added this connections to the expansion connector
2017-08-15 Added square wave output.
2017-08-22 Modified a lot of fields in components parts. BOM generated. Added BOM plugin script.
2017-08-22 Changed some MPN and footprints. BOM updated.
2017-08-22 Added Jack and bnc symbols to schematic.
2017-08-22 Changed trimmer caps MPN and footprints
2017-08-23 Moved some capacitors
2017-08-23 Selected connectors and footprints added.
2017-08-23 Added testpoints to schematic.
2017-08-23 Updated BOM and netlist
2017-08-24 replaced external dc connector: usb instead of pines. Sí, pines
2017-08-24 Updated schematic
2017-08-24 Doing re-routing
2017-08-25 Rerouted with trimmer caps corrected footprints
2017-08-25 Removed 3D of trimmer caps
2017-08-26 Changed 1/4 jack to 1/8 jack
2017-08-28 Changed audio jack in pcb
2017-08-28 Added resistance to control lines to prevent overshoot
2017-08-28 Updated some MPN
2017-08-29 Added BOM generated with kicost
2017-08-29 Updated kicost BOM
2017-08-29 Almost rev1
2017-08-29 Updated MPN to components avalaible in mouser. Updating footprints now ...
2017-08-29 Updated some footprints. Not updated audio jack and BNC.
2017-08-30 Updated jack symbol and footprint
2017-08-30 Highlighted repeated items in BOM
2017-08-30 Updated BNC and USB footprints
2017-08-30 Corrected PN in BOM
2017-08-30 Changed incorrect footprint
2017-08-30 Changed MPN FT2232H to FT2232HL
2017-08-30 New BOM generated with kicost
2017-08-31 Renamed PN: AS4C1M16S->AS4C1M16S-7TCN; MIC5270->MIC5270-3.0YM5-TR; CLC4007->CLC4007ITP14MTR
2017-09-01 Oscillator changed
2017-09-01 Corrected digital part of pcb with new footprints of roms and new oscillators
2017-09-03 Corrected routing in analogue part of board
2017-09-05 Fab files
2017-10-11 New analog front end started. Trying to solve routing in one layer ...
2017-10-17 Finished with routing.
2017-10-17 Modified fcu gnd plane
2017-11-14 New version of mainboard. Corrected errors and modified analog part.
2017-11-14 Reverted changes in PGA and attenuation
2017-11-14 Corrected PCB
2017-11-25 Added pdf with gerbers
2017-11-25 no copper in holes, labels to indicate front and bottom
2017-11-25 Panelización y filmina negativa
2017-12-25 corrected resistors of PGA
2017-12-25 changed ref of adc (2.5V-->2V), and Rf of last amp stage (62K-->51K)
2017-12-25 changed +2V5 regulator: MIC5317-->TLV73325
2017-12-25 changed AC coupling capacitor: 100p-->100n
2017-12-27 corrections in board
2018-02-25 Changed resistance values in last offset stage
2018-03-05 corrected adc protection diode footprint
